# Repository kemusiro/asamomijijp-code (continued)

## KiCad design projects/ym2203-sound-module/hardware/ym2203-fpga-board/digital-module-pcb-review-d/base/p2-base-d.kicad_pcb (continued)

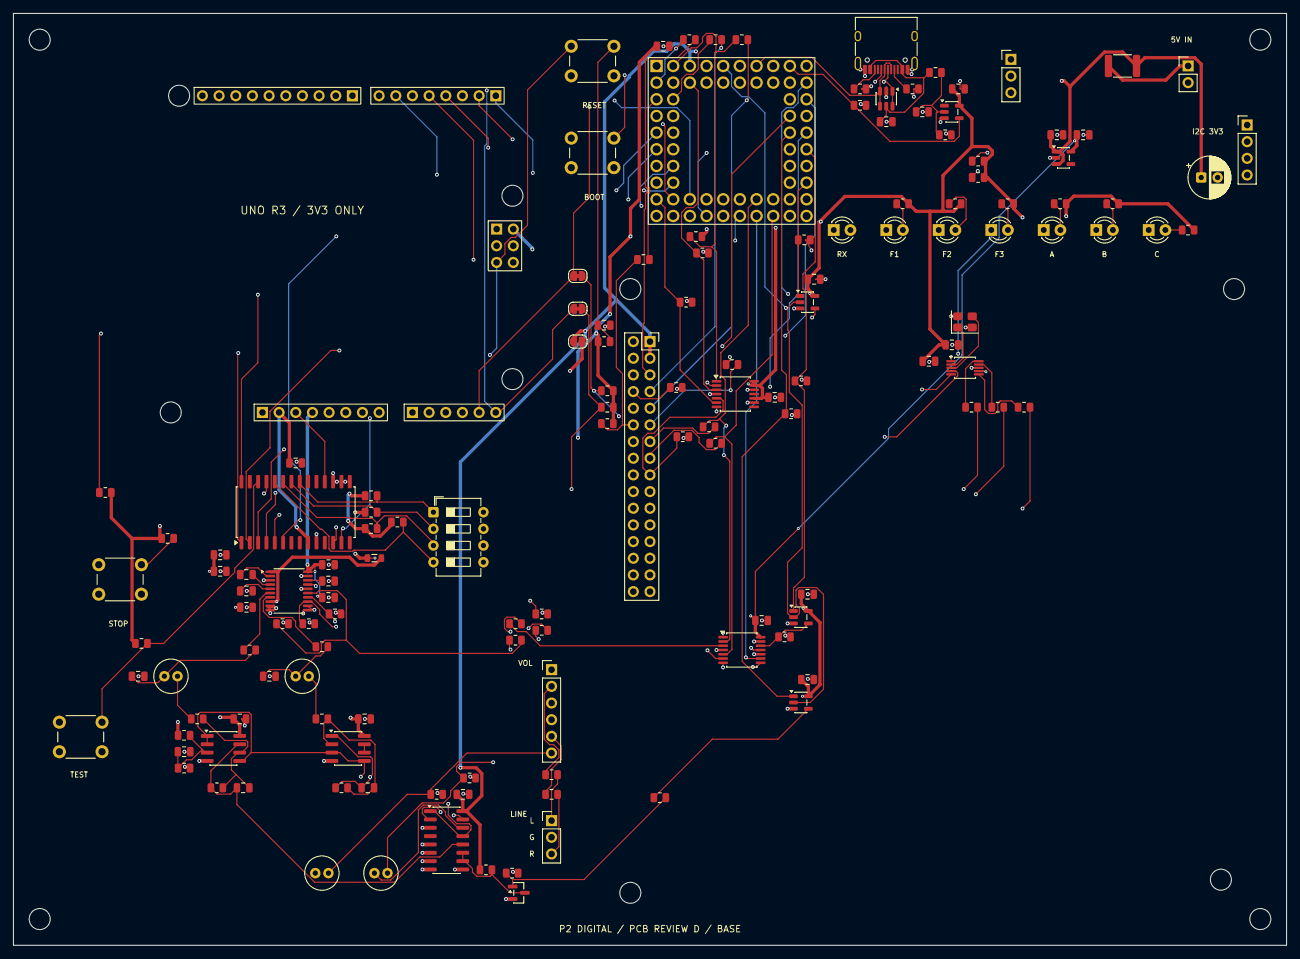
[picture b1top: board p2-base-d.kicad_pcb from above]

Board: 4 copper layers, 194.0 x 142.0 mm, 159 parts (0 on the bottom side), 128 nets.

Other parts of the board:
H1, H2, H3, H4, H5, H6, H7, H8, H9, H10, H11, H12: MountingHole_3.2mm_M3

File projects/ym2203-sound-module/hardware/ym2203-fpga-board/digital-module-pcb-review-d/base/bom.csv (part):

Reference,Value,Footprint,Sheet,Datasheet,Note
MPGA,PGA2350 PIM722 SOCKET,P2D:PGA2350_Socket_64,01-module,https://shop.pimoroni.com/products/pga2350,PGA2350 only on base; accepted reviewB GPIO adopted by user2026-11-16. FreeYM pins andPSRAM47NC. USB resistors already onboard. Firmware port pending.
JHOST,JHOST,Connector_PinHeader_2.54mm:PinHeader_1x04_P2.54mm_Vertical,01-module,,Existing OTHER Pico GP0 SDA / GP1 SCL; 100kHz / 0x42; NO supply pin
JSWD,JSWD,Connector_PinHeader_2.54mm:PinHeader_1x03_P2.54mm_Vertical,01-module,,3.3V SWD probe; never power carrier through probe
SWRESET,RESET,Button_Switch_THT:SW_PUSH_6mm_H4.3mm,01-module,,Two contact numbers; each has two duplicated physical pads in KiCad footprint
SWBOOT,BOOTSEL,Button_Switch_THT:SW_PUSH_6mm_H4.3mm,01-module,,Two contact numbers; each has two duplicated physical pads in KiCad footprint
RRUN,10k,Resistor_SMD:R_0805_2012Metric,01-module,,
CRUN,1n C0G,Capacitor_SMD:C_0805_2012Metric,01-module,,Capacitor body/height and effective capacitance to be checked against final MPN
JPOWER,JPOWER,Connector_PinHeader_2.54mm:PinHeader_1x02_P2.54mm_Vertical,02-power-usb,,Regulated5.1V class2A; verify4.75..5.25V atYM under load. USB VBUS is not a power source.
F1,MF-MSMF150/16X-2 / hold1.5A@23C,Fuse:Fuse_1812_4532Metric,02-power-usb,https://bourns.com/docs/product-datasheets/mf-msmf.pdf,
C1,100u 10V,Capacitor_THT:CP_Radial_D6.3mm_P2.50mm,02-power-usb,,Capacitor body/height and effective capacitance to be checked against final MPN
C2,10u 10V,Capacitor_SMD:C_0805_2012Metric,02-power-usb,,Capacitor body/height and effective capacitance to be checked against final MPN
JUSB,HRO TYPE-C-31-M-12 USB2 DEVICE,Connector_USB:USB_C_Receptacle_HRO_TYPE-C-31-M-12,02-power-usb,http://www.krhro.com/uploads/soft/180320/1-1P320120243.pdf,Self-powered. A6/B6 DP; A7/B7 DM; SBU NC. Verify exact purchased connector drawing before layout release.
RCC1,5.1k 1%,Resistor_SMD:R_0805_2012Metric,02-power-usb,,
RCC2,5.1k 1%,Resistor_SMD:R_0805_2012Metric,02-power-usb,,
UESD,USBLC6-2SC6,Package_TO_SOT_SMD:SOT-23-6,02-power-usb,https://www.st.com/resource/en/datasheet/usblc6-2.pdf,"Place at USB connector, short return. VBUS protection/sense only; no external5V power path."
CVBUS,100n X7R 10V,Capacitor_SMD:C_0805_2012Metric,02-power-usb,,Capacitor body/height and effective capacitance to be checked against final MPN
RVB1,47k 0.1%,Resistor_SMD:R_0805_2012Metric,02-power-usb,,
RVB2,68k 0.1%,Resistor_SMD:R_0805_2012Metric,02-power-usb,,
CVBD,100p C0G,Capacitor_SMD:C_0805_2012Metric,02-power-usb,,Capacitor body/height and effective capacitance to be checked against final MPN
UVBUS,SN74LVC1G17DBVR,Package_TO_SOT_SMD:SOT-23-5,02-power-usb,https://www.ti.com/lit/ds/symlink/sn74lvc1g17.pdf,Schmitt buffer / Ioff; USB VBUS sense to GP46; no power through USB
CVB3,100n X7R 10V,Capacitor_SMD:C_0805_2012Metric,02-power-usb,,Capacitor body/height and effective capacitance to be checked against final MPN
RVB3,100k,Resistor_SMD:R_0805_2012Metric,02-power-usb,,
RPDAC,10k,Resistor_SMD:R_0805_2012Metric,03-default-stop,,
RPLINE,10k,Resistor_SMD:R_0805_2012Metric,03-default-stop,,
U13,Si5351A-B-GT,Package_SO:MSOP-10_3x3mm_P0.5mm,05-clock-ym,https://www.skyworksinc.com/-/media/SkyWorks/SL/documents/pu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,Blank no-boot preset; P2 firmware must disable CLK1/2 and configure CLK0 before reset release
Y1,25MHz CL10pF +/-20ppm,Crystal:Crystal_SMD_3225-4Pin_3.2x2.5mm,05-clock-ym,,ABM8-25.000MHZ-10-1-U-T candidate; ESR/drive and actual footprint need confirmation
C21,100n X7R 10V,Capacitor_SMD:C_0805_2012Metric,05-clock-ym,,Capacitor body/height and effective capacitance to be checked against final MPN
C22,100n X7R 10V,Capacitor_SMD:C_0805_2012Metric,05-clock-ym,,Capacitor body/height and effective capacitance to be checked against final MPN
R37,2.2k,Resistor_SMD:R_0805_2012Metric,05-clock-ym,,
R38,2.2k,Resistor_SMD:R_0805_2012Metric,05-clock-ym,,
R45,2.2k,Resistor_SMD:R_0805_2012Metric,06-dac,,
R46,2.2k,Resistor_SMD:R_0805_2012Metric,06-dac,,
FB1,BLM21PG601SN1 / 600R@100MHz,Inductor_SMD:L_0805_2012Metric,06-dac,,
U17,PCM5102APWR,Package_SO:TSSOP-20_4.4x6.5mm_P0.65mm,06-dac,https://www.ti.com/lit/ds/symlink/pcm5102a.pdf,Stereo FINAL FM+SSG I2S. XSMT mutes all sources. AV3V3 input buffers isolate MCU and AUX rails.
C28,2.2u X7R 10V,Capacitor_SMD:C_0805_2012Metric,06-dac,,Capacitor body/height and effective capacitance to be checked against final MPN
C29,2.2u X7R 10V,Capacitor_SMD:C_0805_2012Metric,06-dac,,Capacitor body/height and effective capacitance to be checked against final MPN
C30,1u X7R 10V,Capacitor_SMD:C_0805_2012Metric,06-dac,,Capacitor body/height and effective capacitance to be checked against final MPN
C31,100n X7R 10V,Capacitor_SMD:C_0805_2012Metric,06-dac,,Capacitor body/height and effective capacitance to be checked against final MPN
C32,100n X7R 10V,Capacitor_SMD:C_0805_2012Metric,06-dac,,Capacitor body/height and effective capacitance to be checked against final MPN
C33,100n X7R 10V,Capacitor_SMD:C_0805_2012Metric,06-dac,,Capacitor body/height and effective capacitance to be checked against final MPN
C34,10u 10V,Capacitor_SMD:C_0805_2012Metric,06-dac,,Capacitor body/height and effective capacitance to be checked against final MPN
C35,10u 10V,Capacitor_SMD:C_0805_2012Metric,06-dac,,Capacitor body/height and effective capacitance to be checked against final MPN
R47,33,Resistor_SMD:R_0805_2012Metric,06-dac,,
R48,33,Resistor_SMD:R_0805_2012Metric,06-dac,,
R49,33,Resistor_SMD:R_0805_2012Metric,06-dac,,
R50,10k,Resistor_SMD:R_0805_2012Metric,06-dac,,
U18,MCP6022-I/SN,Package_SO:SOIC-8_3.9x4.9mm_P1.27mm,07-analog,https://ww1.microchip.com/downloads/en/DeviceDoc/20001685E.pdf,
C36,100n X7R 10V,Capacitor_SMD:C_0805_2012Metric,07-analog,,Capacitor body/height and effective capacitance to be checked against final MPN
R51,10k 1%,Resistor_SMD:R_0805_2012Metric,07-analog,,
R52,10k 1%,Resistor_SMD:R_0805_2012Metric,07-analog,,
C37,10u 10V,Capacitor_SMD:C_0805_2012Metric,07-analog,,Capacitor body/height and effective capacitance to be checked against final MPN
R53,470,Resistor_SMD:R_0805_2012Metric,07-analog,,
C38,2.2n C0G,Capacitor_SMD:C_0805_2012Metric,07-analog,,Capacitor body/height and effective capacitance to be checked against final MPN
CA3,4.7u bipolar 10V,Capacitor_THT:C_Radial_D5.0mm_H11.0mm_P2.00mm,07-analog,,Capacitor body/height and effective capacitance to be checked against final MPN
RM3,100k 1%,Resistor_SMD:R_0805_2012Metric,07-analog,,
R54,47k 1%,Resistor_SMD:R_0805_2012Metric,07-analog,,
C39,47p C0G,Capacitor_SMD:C_0805_2012Metric,07-analog,,Capacitor body/height and effective capacitance to be checked against final MPN
U19,CD74HC4053M,Package_SO:SOIC-16_3.9x9.9mm_P1.27mm,07-analog,https://www.ti.com/lit/ds/symlink/cd74hc4053.pdf,Default A=HIGH selects VREF; active LINE_RUN transistor selects audio
C40,100n X7R 10V,Capacitor_SMD:C_0805_2012Metric,07-analog,,Capacitor body/height and effective capacitance to be checked against final MPN
Q5,MMBT3904LT1G,Package_TO_SOT_SMD:SOT-23,07-analog,https://www.onsemi.com/pdf/datasheet/mmbt3904lt1-d.pdf,
R55,10k,Resistor_SMD:R_0805_2012Metric,07-analog,,
R56,100k,Resistor_SMD:R_0805_2012Metric,07-analog,,
R57,10k,Resistor_SMD:R_0805_2012Metric,07-analog,,
C41,4.7u bipolar 10V,Capacitor_THT:C_Radial_D5.0mm_H11.0mm_P2.00mm,07-analog,,Capacitor body/height and effective capacitance to be checked against final MPN
R58,100k,Resistor_SMD:R_0805_2012Metric,07-analog,,
JPOT,JPOT,Connector_PinHeader_2.54mm:PinHeader_1x06_P2.54mm_Vertical,07-analog,,"Dual A10k offboard pot; CW=3/6, wipers 2/5, CCW=1/4"
R59,100,Resistor_SMD:R_0805_2012Metric,07-analog,,
R60,100,Resistor_SMD:R_0805_2012Metric,07-analog,,
JLINE,JLINE,Connector_PinHeader_2.54mm:PinHeader_1x03_P2.54mm_Vertical,07-analog,,"Line output, not headphone driver"
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
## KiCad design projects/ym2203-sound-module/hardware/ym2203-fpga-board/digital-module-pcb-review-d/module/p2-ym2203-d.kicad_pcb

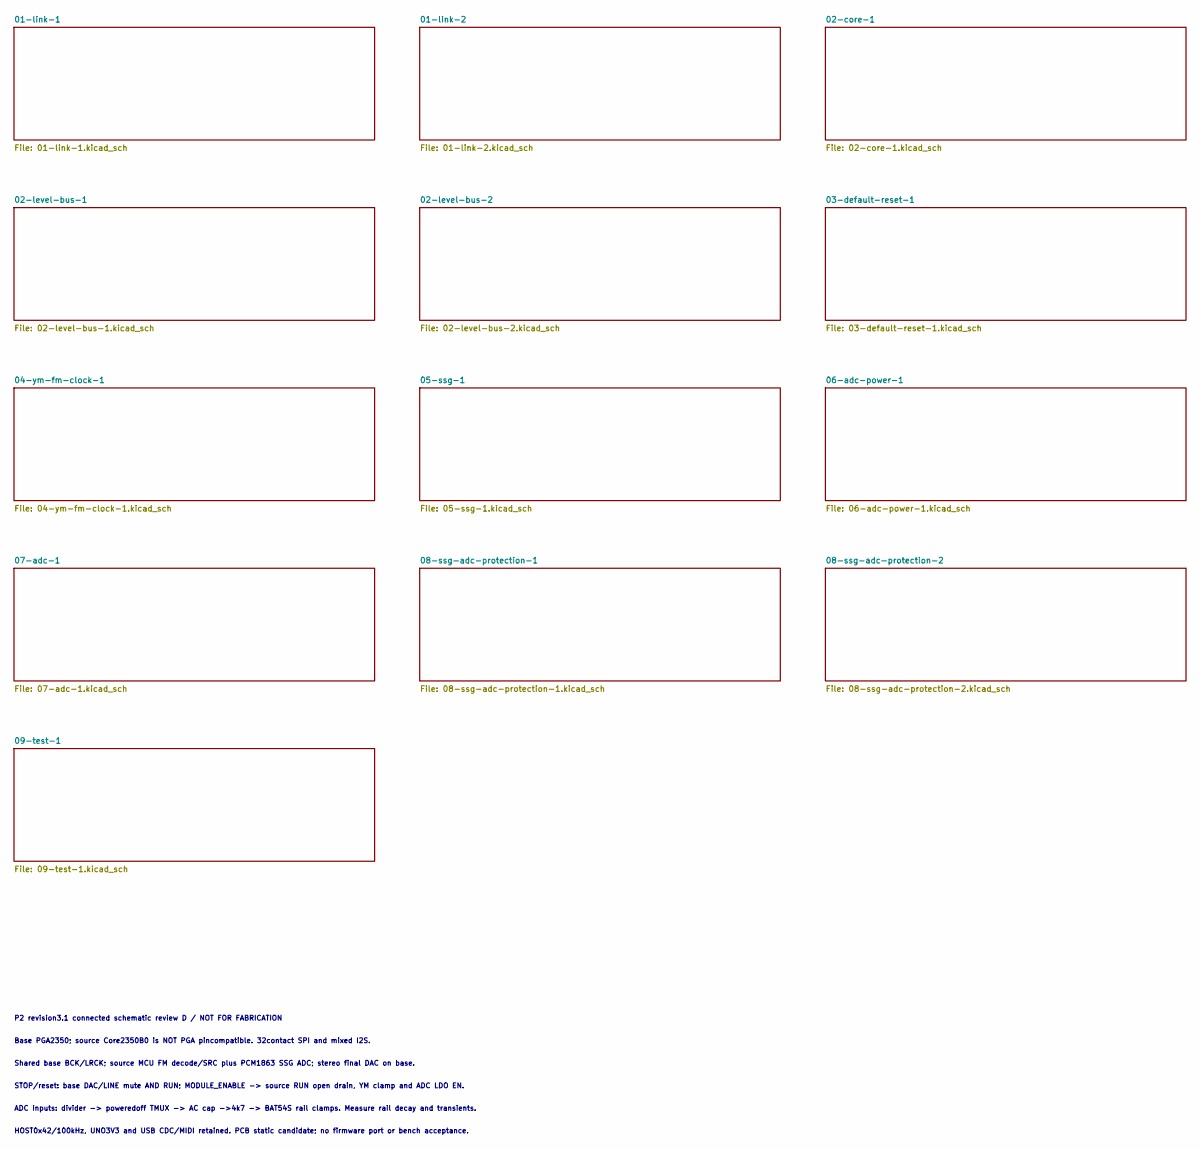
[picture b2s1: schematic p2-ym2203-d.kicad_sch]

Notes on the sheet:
P2 revision3.1 connected schematic review D / NOT FOR FABRICATION
Base PGA2350; source Core2350B0 is NOT PGA pincompatible. 32contact SPI and mixed I2S.
Shared base BCK/LRCK; source MCU FM decode/SRC plus PCM1863 SSG ADC; stereo final DAC on base.
STOP/reset: base DAC/LINE mute AND RUN; MODULE_ENABLE -> source RUN open drain, YM clamp and ADC LDO EN.
ADC inputs: divider -> poweredoff TMUX -> AC cap ->4k7 -> BAT54S rail clamps. Measure rail decay and transients.
HOST0x42/100kHz, UNO3V3 and USB CDC/MIDI retained. PCB static candidate; no firmware port or bench acceptance.

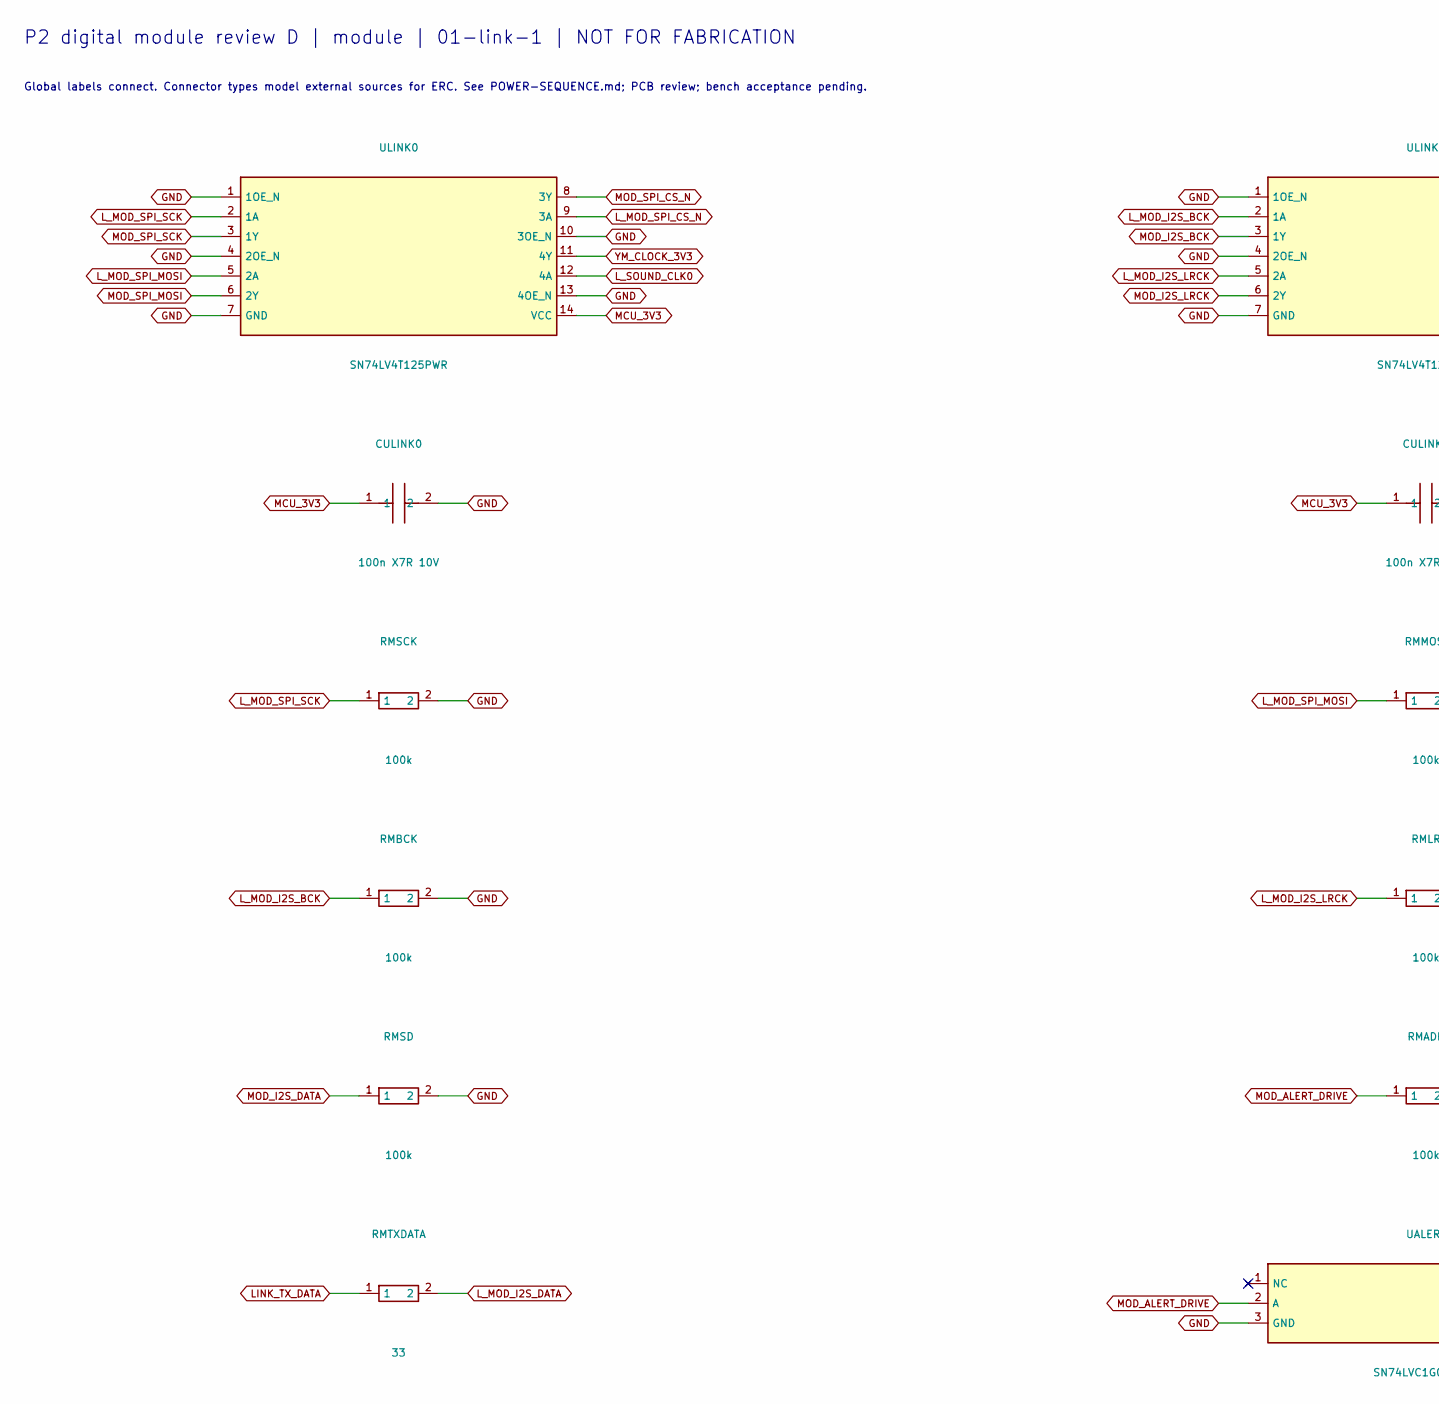
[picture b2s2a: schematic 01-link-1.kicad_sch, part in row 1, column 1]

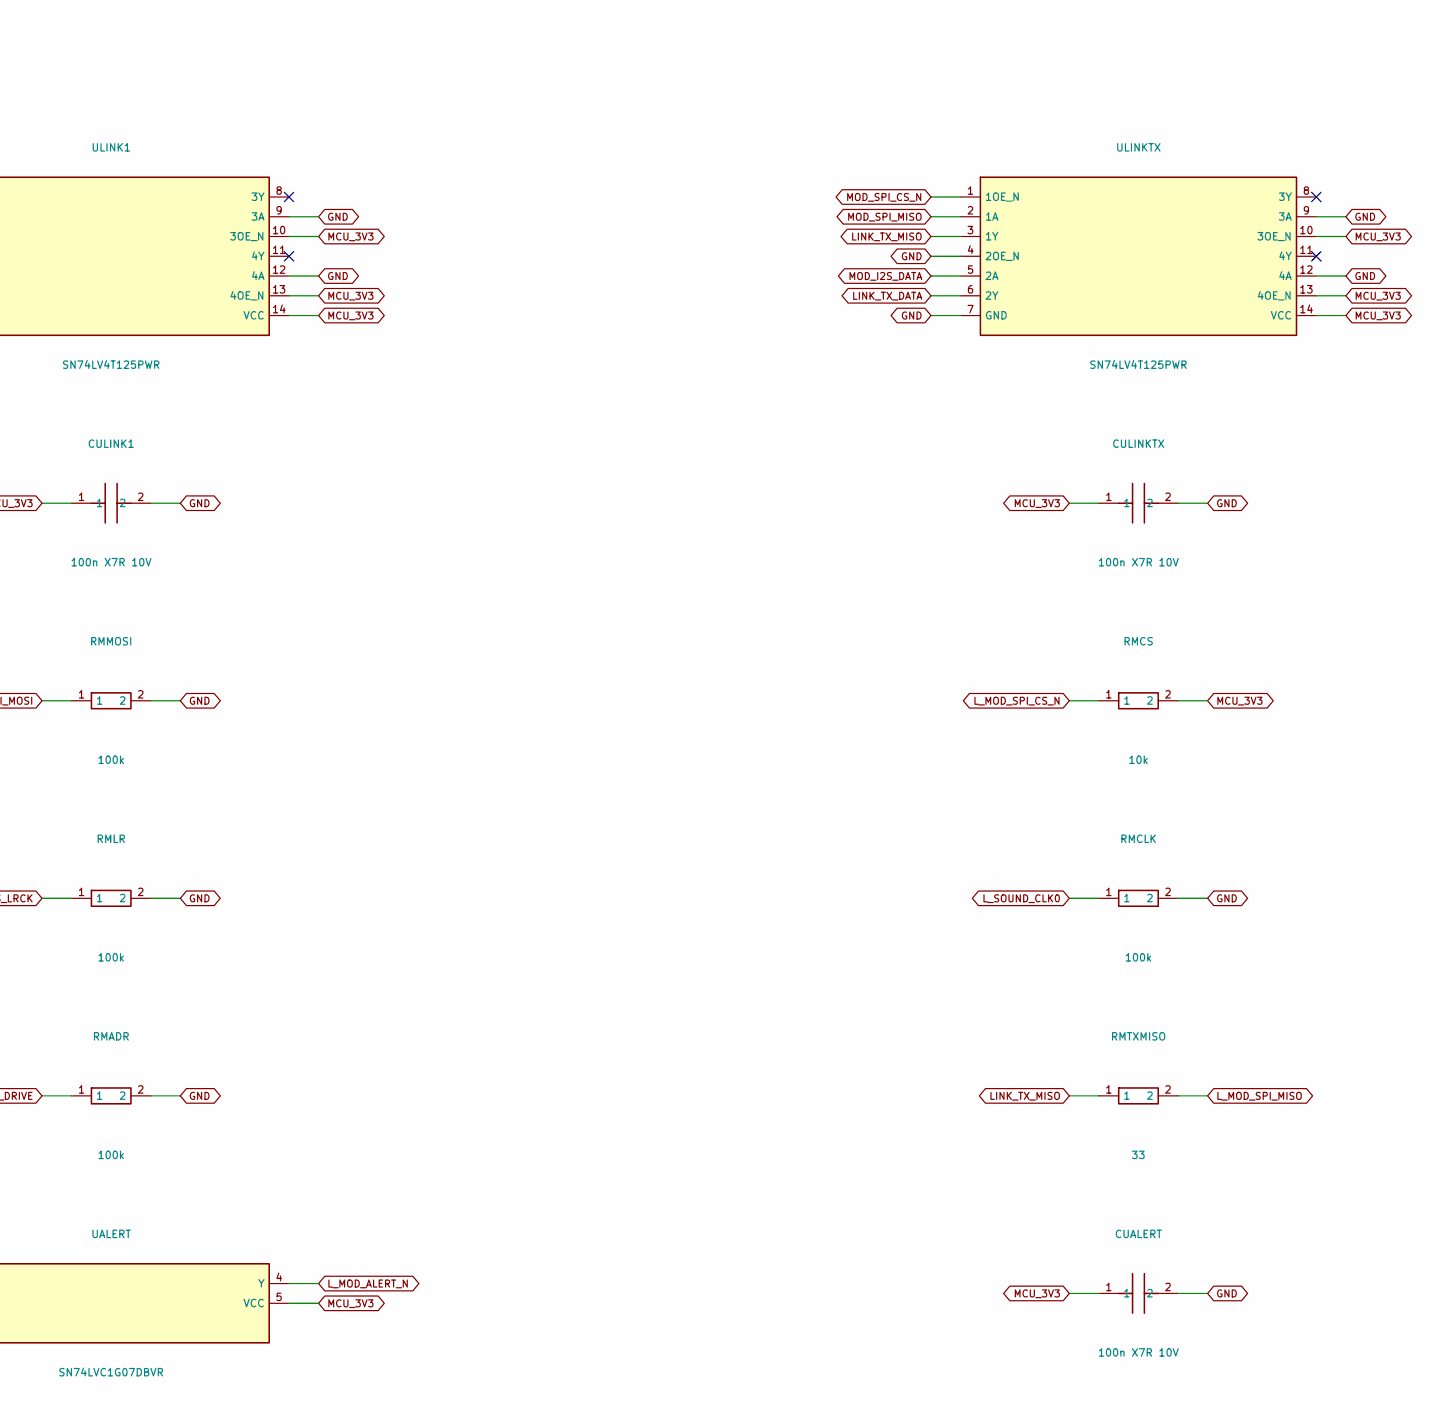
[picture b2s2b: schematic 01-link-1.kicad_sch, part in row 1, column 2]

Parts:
CUALERT: 100n X7R 10V; C_0805_2012Metric
CULINK0, CULINK1: 100n X7R 10V; C_0805_2012Metric
CULINKTX: 100n X7R 10V; C_0805_2012Metric
RMADR: 100k; R_0805_2012Metric
RMBCK: 100k; R_0805_2012Metric
RMCLK: 100k; R_0805_2012Metric
RMCS: 10k; R_0805_2012Metric
RMLR: 100k; R_0805_2012Metric
RMMOSI: 100k; R_0805_2012Metric
RMSCK: 100k; R_0805_2012Metric
RMSD: 100k; R_0805_2012Metric
RMTXDATA: 33; R_0805_2012Metric
RMTXMISO: 33; R_0805_2012Metric
UALERT: SN74LVC1G07DBVR; SOT-23-5
ULINK0, ULINK1: SN74LV4T125PWR; TSSOP-14_4.4x5mm_P0.65mm
ULINKTX: SN74LV4T125PWR; TSSOP-14_4.4x5mm_P0.65mm

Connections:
GND: CUALERT.2, CULINK0.2, CULINK1.2, CULINKTX.2, RMADR.2, RMBCK.2, RMCLK.2, RMLR.2, RMMOSI.2, RMSCK.2, RMSD.2, UALERT.3 (GND), ULINK0.1 (1OE_N), ULINK0.4 (2OE_N), ULINK0.7 (GND), ULINK0.10 (3OE_N), ULINK0.13 (4OE_N), ULINK1.1 (1OE_N), ULINK1.4 (2OE_N), ULINK1.7 (GND), ULINK1.9 (3A), ULINK1.12 (4A), ULINKTX.4 (2OE_N), ULINKTX.7 (GND), ULINKTX.9 (3A), ULINKTX.12 (4A); also elsewhere on the board
LINK_TX_DATA: RMTXDATA.1, ULINKTX.6 (2Y)
LINK_TX_MISO: RMTXMISO.1, ULINKTX.3 (1Y)
L_MOD_ALERT_N: UALERT.4 (Y); also elsewhere on the board
L_MOD_I2S_BCK: RMBCK.1, ULINK1.2 (1A); also elsewhere on the board
L_MOD_I2S_DATA: RMTXDATA.2; also elsewhere on the board
L_MOD_I2S_LRCK: RMLR.1, ULINK1.5 (2A); also elsewhere on the board
L_MOD_SPI_CS_N: RMCS.1, ULINK0.9 (3A); also elsewhere on the board
L_MOD_SPI_MISO: RMTXMISO.2; also elsewhere on the board
L_MOD_SPI_MOSI: RMMOSI.1, ULINK0.5 (2A); also elsewhere on the board
L_MOD_SPI_SCK: RMSCK.1, ULINK0.2 (1A); also elsewhere on the board
L_SOUND_CLK0: RMCLK.1, ULINK0.12 (4A); also elsewhere on the board
MCU_3V3: CUALERT.1, CULINK0.1, CULINK1.1, CULINKTX.1, RMCS.2, UALERT.5 (VCC), ULINK0.14 (VCC), ULINK1.10 (3OE_N), ULINK1.13 (4OE_N), ULINK1.14 (VCC), ULINKTX.10 (3OE_N), ULINKTX.13 (4OE_N), ULINKTX.14 (VCC); also elsewhere on the board
MOD_ALERT_DRIVE: RMADR.1, UALERT.2 (A); also elsewhere on the board
MOD_I2S_BCK: ULINK1.3 (1Y); also elsewhere on the board
MOD_I2S_DATA: RMSD.1, ULINKTX.5 (2A); also elsewhere on the board
MOD_I2S_LRCK: ULINK1.6 (2Y); also elsewhere on the board
MOD_SPI_CS_N: ULINK0.8 (3Y), ULINKTX.1 (1OE_N); also elsewhere on the board
MOD_SPI_MISO: ULINKTX.2 (1A); also elsewhere on the board
MOD_SPI_MOSI: ULINK0.6 (2Y); also elsewhere on the board
MOD_SPI_SCK: ULINK0.3 (1Y); also elsewhere on the board
YM_CLOCK_3V3: ULINK0.11 (4Y); also elsewhere on the board

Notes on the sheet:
P2 digital module review D | module | 01-link-1 | NOT FOR FABRICATION
Global labels connect. Connector types model external sources for ERC. See POWER-SEQUENCE.md; PCB review; bench acceptance pending.

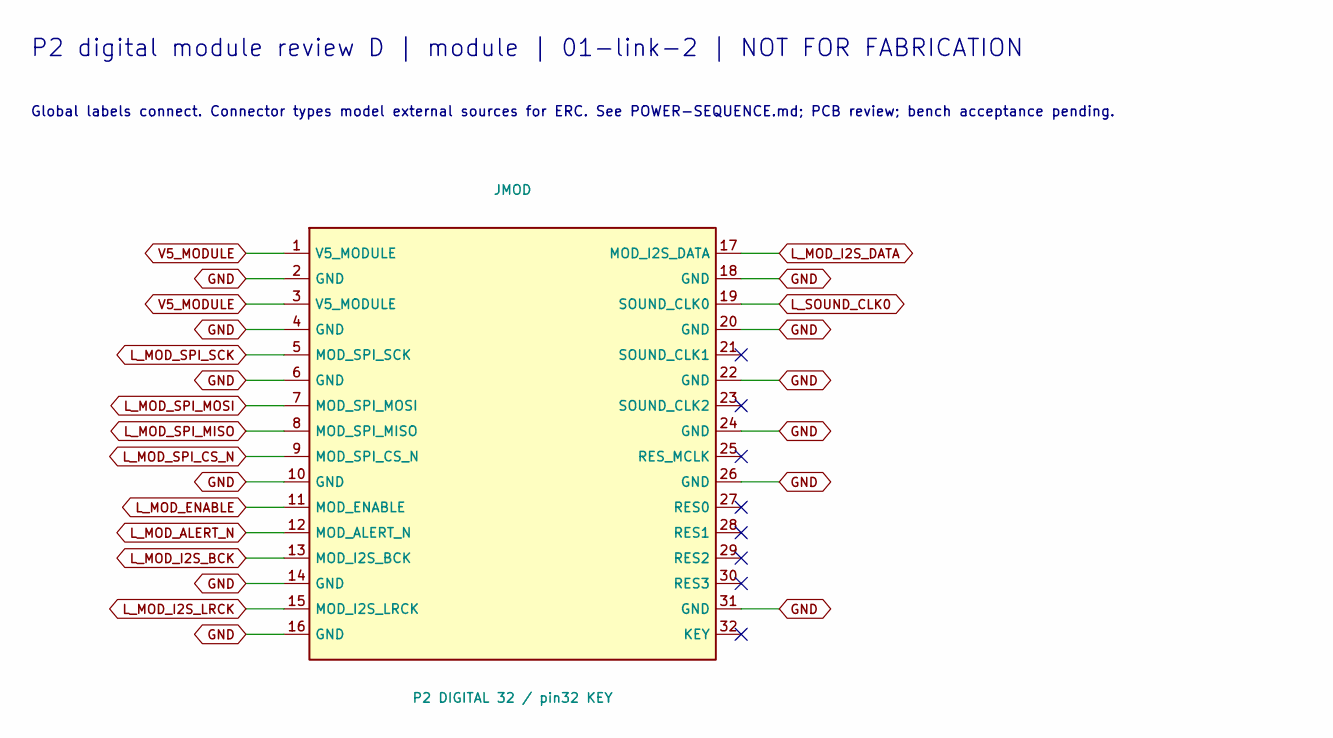
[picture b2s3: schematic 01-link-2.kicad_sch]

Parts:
JMOD: P2 DIGITAL 32 / pin32 KEY; PinHeader_2x16_P2.54mm_Vertical

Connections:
GND: JMOD.2 (GND), JMOD.4 (GND), JMOD.6 (GND), JMOD.10 (GND), JMOD.14 (GND), JMOD.16 (GND), JMOD.18 (GND), JMOD.20 (GND), JMOD.22 (GND), JMOD.24 (GND), JMOD.26 (GND), JMOD.31 (GND); also elsewhere on the board
L_MOD_ALERT_N: JMOD.12 (MOD_ALERT_N); also elsewhere on the board
L_MOD_ENABLE: JMOD.11 (MOD_ENABLE); also elsewhere on the board
L_MOD_I2S_BCK: JMOD.13 (MOD_I2S_BCK); also elsewhere on the board
L_MOD_I2S_DATA: JMOD.17 (MOD_I2S_DATA); also elsewhere on the board
L_MOD_I2S_LRCK: JMOD.15 (MOD_I2S_LRCK); also elsewhere on the board
L_MOD_SPI_CS_N: JMOD.9 (MOD_SPI_CS_N); also elsewhere on the board
L_MOD_SPI_MISO: JMOD.8 (MOD_SPI_MISO); also elsewhere on the board
L_MOD_SPI_MOSI: JMOD.7 (MOD_SPI_MOSI); also elsewhere on the board
L_MOD_SPI_SCK: JMOD.5 (MOD_SPI_SCK); also elsewhere on the board
L_SOUND_CLK0: JMOD.19 (SOUND_CLK0); also elsewhere on the board
V5_MODULE: JMOD.1 (V5_MODULE), JMOD.3 (V5_MODULE); also elsewhere on the board

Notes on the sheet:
P2 digital module review D | module | 01-link-2 | NOT FOR FABRICATION
Global labels connect. Connector types model external sources for ERC. See POWER-SEQUENCE.md; PCB review; bench acceptance pending.

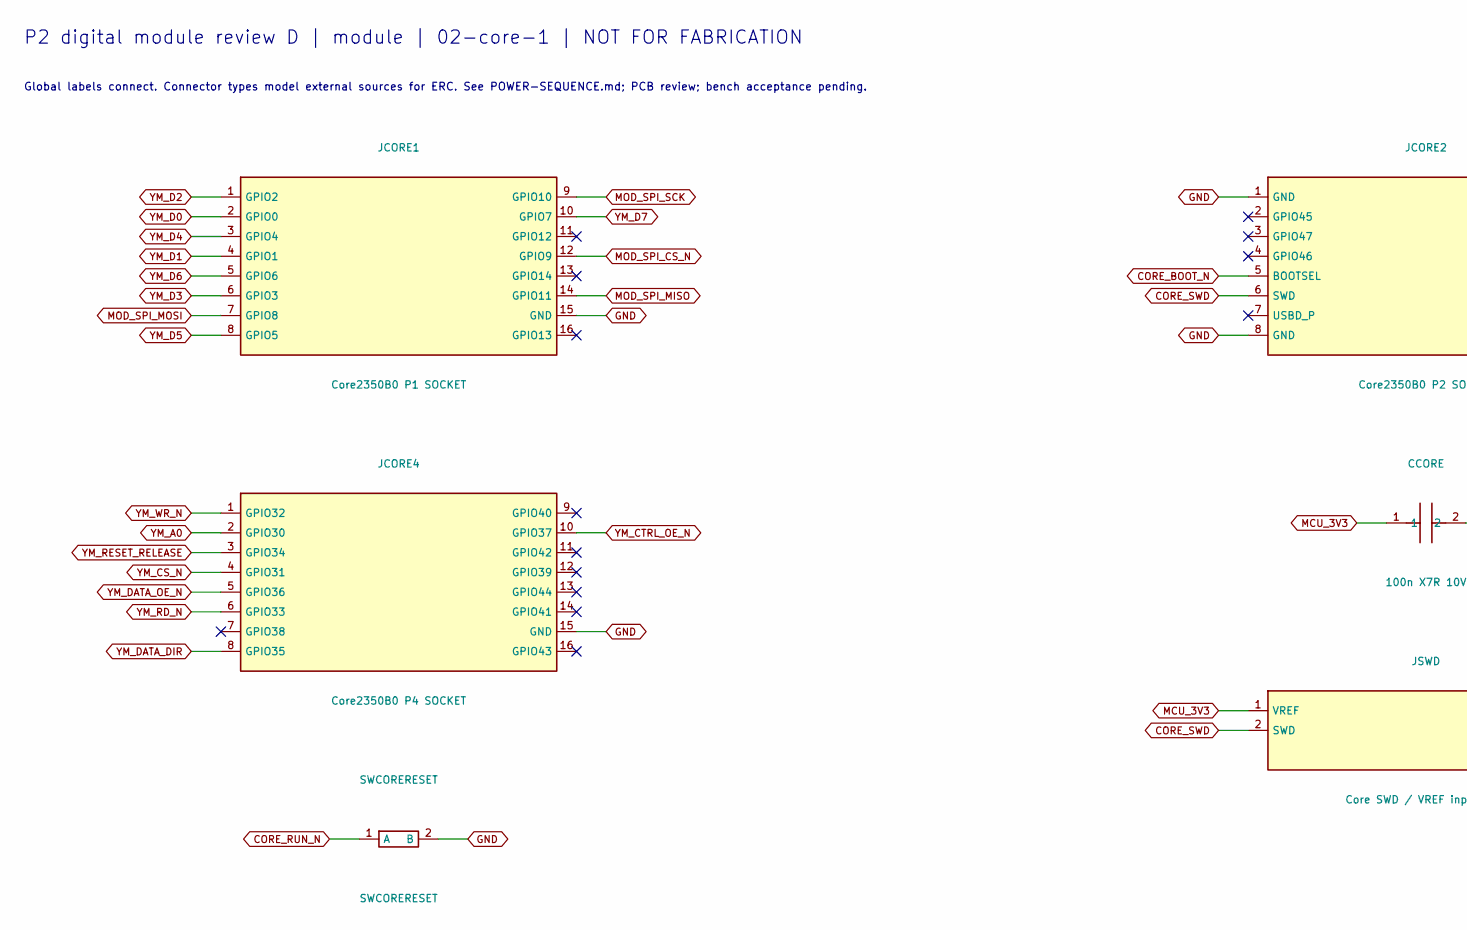
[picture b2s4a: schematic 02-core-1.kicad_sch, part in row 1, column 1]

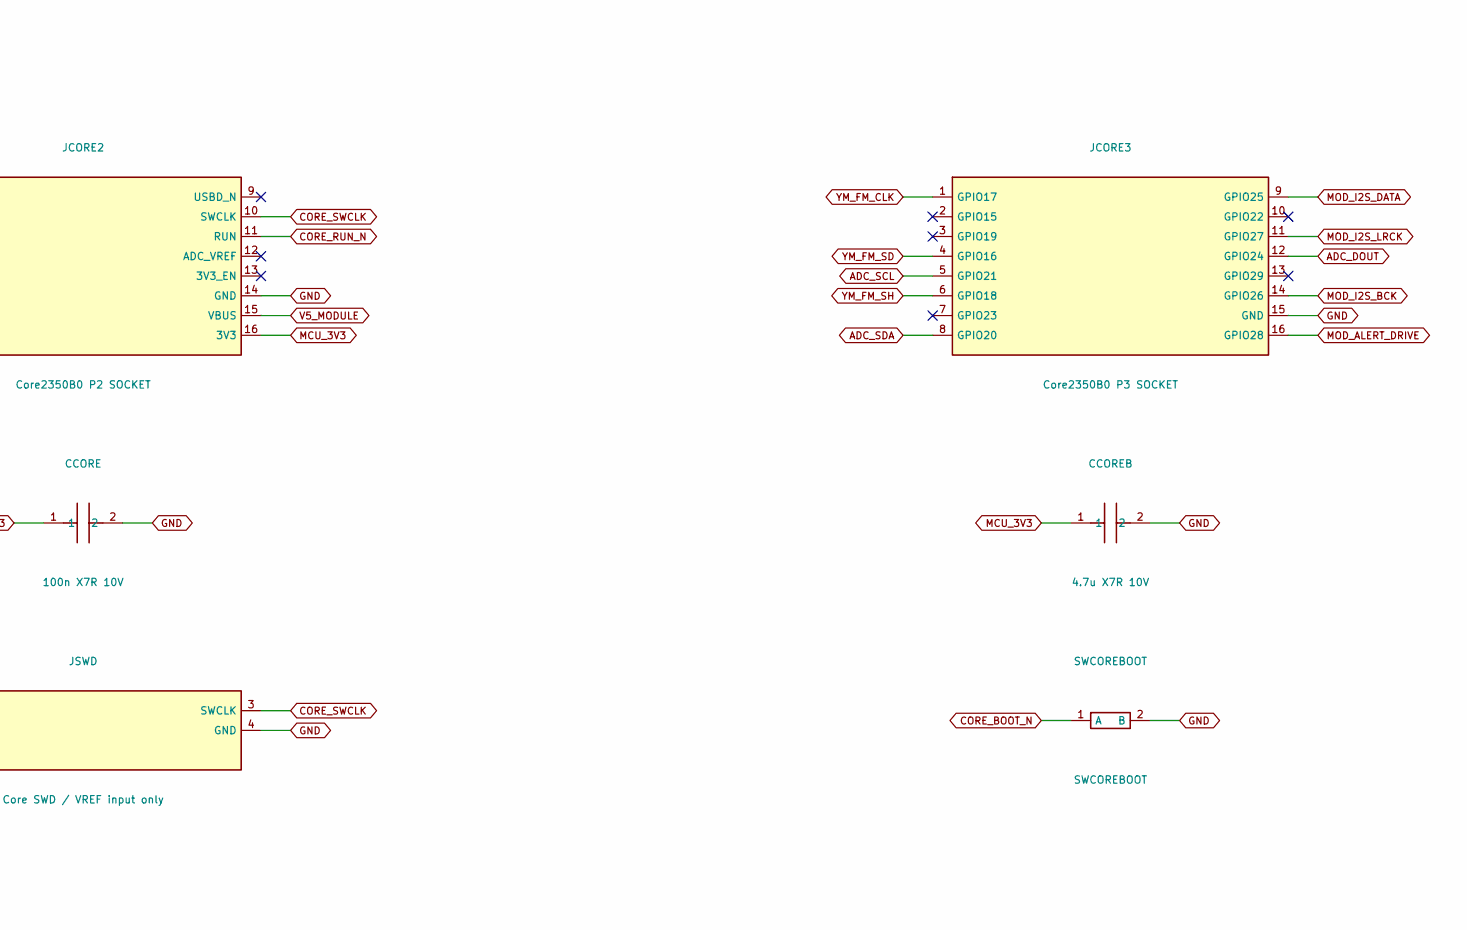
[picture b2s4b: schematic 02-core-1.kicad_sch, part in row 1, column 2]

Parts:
CCORE: 100n X7R 10V; C_0805_2012Metric
CCOREB: 4.7u X7R 10V; C_0805_2012Metric
JCORE1: Core2350B0 P1 SOCKET; Core2350B0_P1_IndividualSockets
JCORE2: Core2350B0 P2 SOCKET; Core2350B0_P2_IndividualSockets
JCORE3: Core2350B0 P3 SOCKET; Core2350B0_P3_IndividualSockets
JCORE4: Core2350B0 P4 SOCKET; Core2350B0_P4_IndividualSockets
JSWD: Core SWD / VREF input only; PinHeader_1x04_P2.54mm_Vertical
SWCOREBOOT: SWCOREBOOT; SW_PUSH_6mm_H4.3mm
SWCORERESET: SWCORERESET; SW_PUSH_6mm_H4.3mm

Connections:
ADC_DOUT: JCORE3.12 (GPIO24); also elsewhere on the board
ADC_SCL: JCORE3.5 (GPIO21); also elsewhere on the board
ADC_SDA: JCORE3.8 (GPIO20); also elsewhere on the board
CORE_BOOT_N: JCORE2.5 (BOOTSEL), SWCOREBOOT.1 (A)
CORE_RUN_N: JCORE2.11 (RUN), SWCORERESET.1 (A); also elsewhere on the board
CORE_SWCLK: JCORE2.10 (SWCLK), JSWD.3 (SWCLK)
CORE_SWD: JCORE2.6 (SWD), JSWD.2 (SWD)
GND: CCORE.2, CCOREB.2, JCORE1.15 (GND), JCORE2.1 (GND), JCORE2.8 (GND), JCORE2.14 (GND), JCORE3.15 (GND), JCORE4.15 (GND), JSWD.4 (GND), SWCOREBOOT.2 (B), SWCORERESET.2 (B); also elsewhere on the board
MCU_3V3: CCORE.1, CCOREB.1, JCORE2.16 (3V3), JSWD.1 (VREF); also elsewhere on the board
MOD_ALERT_DRIVE: JCORE3.16 (GPIO28); also elsewhere on the board
MOD_I2S_BCK: JCORE3.14 (GPIO26); also elsewhere on the board
MOD_I2S_DATA: JCORE3.9 (GPIO25); also elsewhere on the board
MOD_I2S_LRCK: JCORE3.11 (GPIO27); also elsewhere on the board
MOD_SPI_CS_N: JCORE1.12 (GPIO9); also elsewhere on the board
MOD_SPI_MISO: JCORE1.14 (GPIO11); also elsewhere on the board
MOD_SPI_MOSI: JCORE1.7 (GPIO8); also elsewhere on the board
MOD_SPI_SCK: JCORE1.9 (GPIO10); also elsewhere on the board
V5_MODULE: JCORE2.15 (VBUS); also elsewhere on the board
YM_A0: JCORE4.2 (GPIO30); also elsewhere on the board
YM_CS_N: JCORE4.4 (GPIO31); also elsewhere on the board
YM_CTRL_OE_N: JCORE4.10 (GPIO37); also elsewhere on the board
YM_D0: JCORE1.2 (GPIO0); also elsewhere on the board
YM_D1: JCORE1.4 (GPIO1); also elsewhere on the board
YM_D2: JCORE1.1 (GPIO2); also elsewhere on the board
YM_D3: JCORE1.6 (GPIO3); also elsewhere on the board
YM_D4: JCORE1.3 (GPIO4); also elsewhere on the board
YM_D5: JCORE1.8 (GPIO5); also elsewhere on the board
YM_D6: JCORE1.5 (GPIO6); also elsewhere on the board
YM_D7: JCORE1.10 (GPIO7); also elsewhere on the board
YM_DATA_DIR: JCORE4.8 (GPIO35); also elsewhere on the board
YM_DATA_OE_N: JCORE4.5 (GPIO36); also elsewhere on the board
YM_FM_CLK: JCORE3.1 (GPIO17); also elsewhere on the board
YM_FM_SD: JCORE3.4 (GPIO16); also elsewhere on the board
YM_FM_SH: JCORE3.6 (GPIO18); also elsewhere on the board
YM_RD_N: JCORE4.6 (GPIO33); also elsewhere on the board
YM_RESET_RELEASE: JCORE4.3 (GPIO34); also elsewhere on the board
YM_WR_N: JCORE4.1 (GPIO32); also elsewhere on the board

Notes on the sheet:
P2 digital module review D | module | 02-core-1 | NOT FOR FABRICATION
Global labels connect. Connector types model external sources for ERC. See POWER-SEQUENCE.md; PCB review; bench acceptance pending.
